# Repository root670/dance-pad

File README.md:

# 8020 Extruded Aluminum Dance Pad

*StepMania: Way more fun than a Pelaton bike.*

4-panel dance pad project using a frame built out of 30mm profile 8020
("T-Slot") extruded aluminum including a bar with 9 arrow panels following a
similar design to StepManiaX pads. Each directional arrow has a PCB containing
25 WS2812B RGB LEDs and 4 FSR sensors connected to a Main PCB that acts as a
breakout for a Teensy 4.1.

The firmware reads values from 16 sensors and reports them as gamepad inputs.
I'm using homemade sensors created with two 150mm strips of 1/4" copper tape
attached to 160mm x 20mm transparency film with 4mil Velostat placed across the
top. Wires are soldered to each of the copper tape strips and terminate to
JST-XE connectors at the end to connect to the Arrow Panel PCB. According to
papers I've read, creating FSR in this way will likely lead to less drifting
over time compared to "sandwich" style sensors where Velostat is placed between
two pieces of copper tape. This is similar to the method used by
commercially-produced FSRs.

## Motivation

There has been a ton of interest in using force sensitive resistors in dance
pads recently to replace contact-based sensors and many designs have been
created. I decided to create a design for a full pad that is durable but doesn't
require power tools to build. I also wanted to gain experience using Inventor
and KiCad and share my design with others who may find it useful. It's certainly
not the best design, but the experience I've gained in the process is
invaluable.

Having personal projects to come back to is a great and productive way to
improve your creative and technical skills, especially during COVID times. And
when the project involves maintaining your physical health, that's even better! I
can't stress enough how rewarding it is to start a project, work on in over the
course of a few months, and see it through to completion. Soapbox aside, I
highly recommend attempting projects for things that seem slightly out of your
abilities. You might be surprised what you're capable of if you stick with it.

## Directory Structure

* `Frame`: Inventor project for the aluminum frame. It houses nine 276mm x 276mm
  x 12mm cast acrylic panels with 2mm clearance between each edge. The back of
  the frame has slots for securing a bar.

* `Arrow PCB`: 2 layer 200mm x 200mm PCB used within each arrow containing 25
  WS2812B V5 LEDs arranged in an alternating 4,3 grid pattern and pins for 4
  FSRs connected using JST-XH and JST-ZE connectors. Created in KiCad. Each FSR
  uses a 330 ohm pull down resistor to ground. The board is connected to the
  Main PCB using a CAT6 cable for the four sensors and screw terminals for the
  LED power, ground, and data lines. The PCB can be rotated to the best location
  to route wires to the Main PCB by denoting the location in the firmware.
  M4-sized terminals are on the corners of the PCB so it can be mounted to the
  frame using 3D printed parts (TODO).

* `Main PCB`: 2 layer ~100mm x ~100mm breakout board for a Teensy 4.1. Wires
  RJ45 connectors for connections coming from 4 Arrow PCBs and screw terminals
  for up 5 LED strands interfaced through 3.3V to 5V logic converters. The
  sensor wires are decoupled with 3.3v wires in the cable to minimize
  interference. Has M4-sized screw terminal to attach to 3D printed mounting
  hardware (TODO).

* `Configurator`: Application to configure and debug the pad written in Python.
  Communicates with the firmware using a serial connection.

* `Firmware`: Code that runs on the Teensy. Reads sensor values, listens for
  serial messages, and controls the LEDs. Uses fixed timings for sending Joypad
  reports and updating the LEDs. The goal is for it to be easy enough to modify
  to support different pad layouts (i.e. 5 panel StepManiaX or Pump It Up pads)

* `Supplemental`: Various helper scripts and files related to this project. All
  of these are optional but may be useful depending on you setup.

## Status

The frame, acrylic panels, and PCB designs have been finalized, fabricated, and
assembled.

The arrows have counter bore screws but I made the larger part of the counter
bore too small (It's a 9.53mm counterbore for a 7.94mm through hole, leaving
~0.8mm radius for the counterbore. Whoops.). It's large enough to fit
button-head M5 screws with a 3D printed spacer but M6 socket and button head
screws will not fit unfortunately. These will work fine with M5 screws but the
lesson learned is to not hastily order things like this in the future :-).

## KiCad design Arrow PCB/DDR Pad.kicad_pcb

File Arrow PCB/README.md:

# Arrow Panel PCB

Board placed under each panel. Houses 25 WS2812B V5 RGB LEDs and connects to 4
FSR sensors using JST-XE or JST-ZH connectors. Connects back to the Main PCB
using a CAT6 cable for the sensors and cables secured to a screw terminal for
the lights.

## Notes

* The pull down resistor used for each sensor may need to be adjusted depending
  on the sensors being used.
* The board requires the "V5" revision of the WS2812B LEDs. The advantage of
  this version is that have an internal capacitor so you don't the need to place
  an external capacitor between the positive voltage and ground pins. If an
  older version is used the LEDs will likely be damaged when they receive power.

## Issues

* I was unable to get the LEDs to work reliably using multiple 3.3v and 5v
  microcontrollers and WS2812B libraries. I believe there is something wrong
  with my design or the LEDs sourced by LCSC were not actually the 5V
  variations. LCSC has been unable to confirm if they are actually the V5
  version.
* The PCB is too big to fit within the frame underneath the panels when using
  corner brackets. As a workaround the PCBs need to be placed underneath the
  frame.

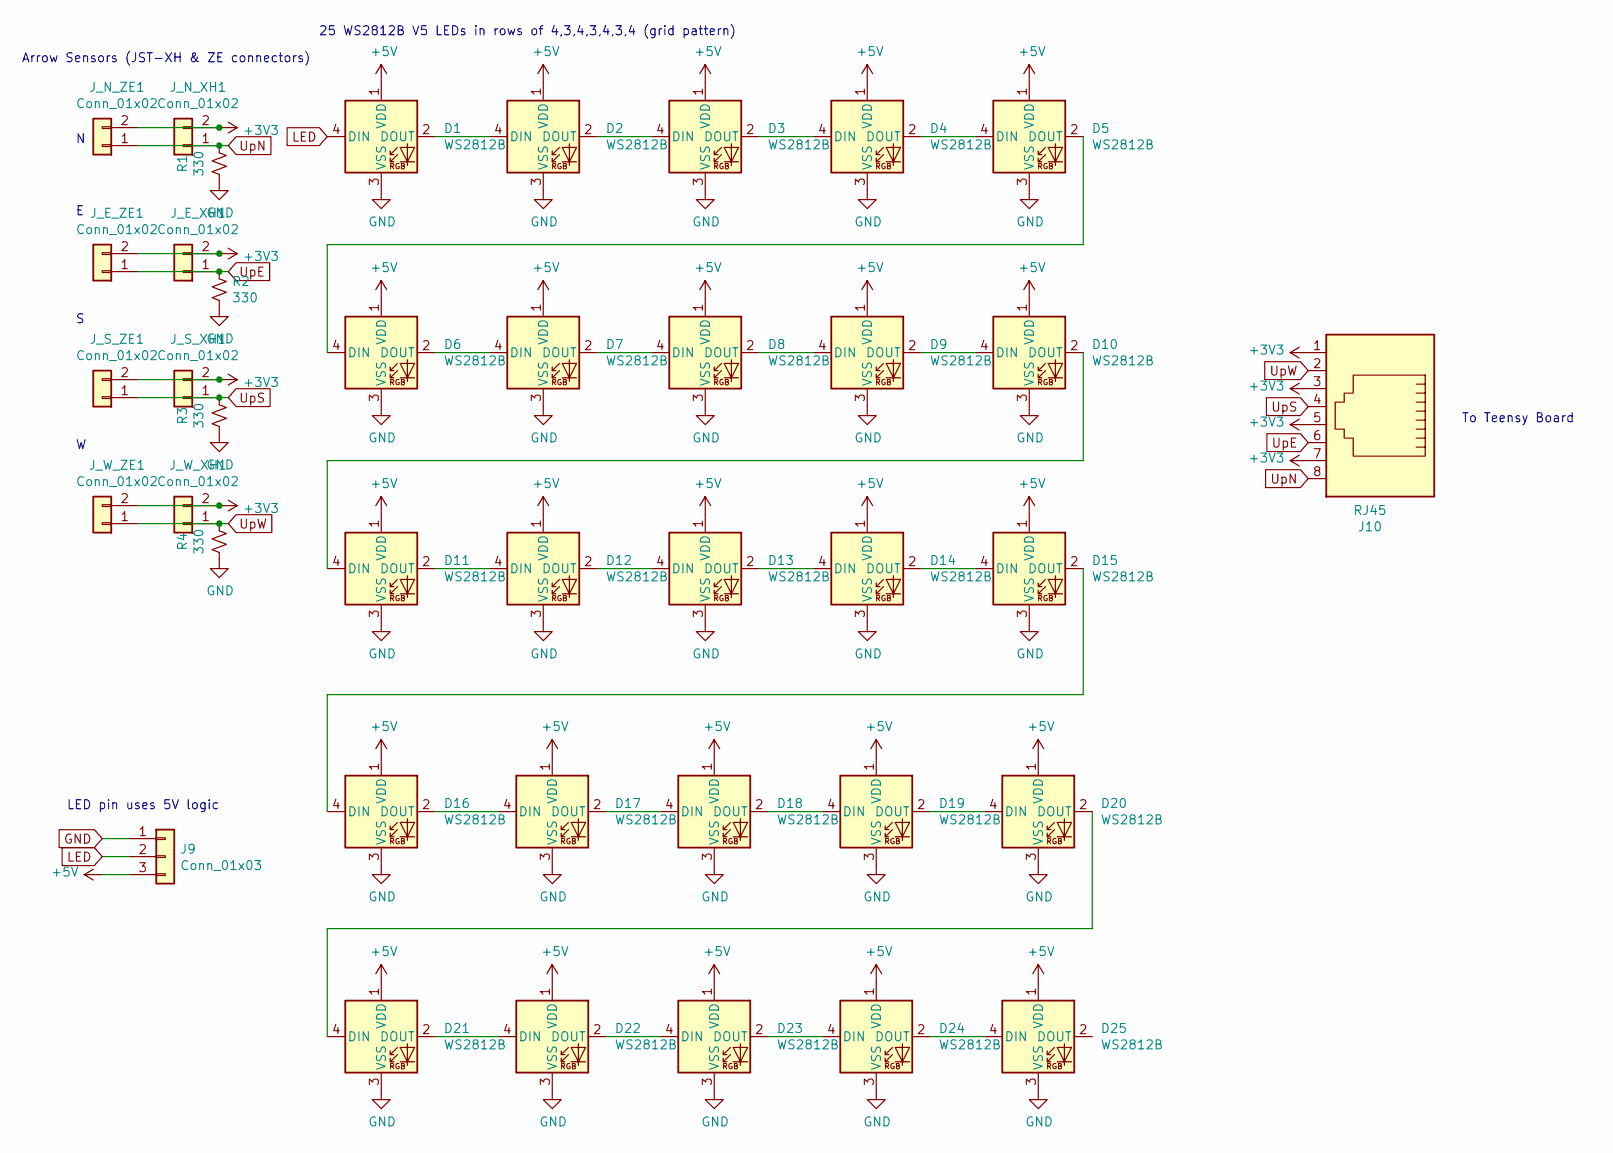
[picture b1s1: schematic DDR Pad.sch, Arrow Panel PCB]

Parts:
D1, D2, D3, D4, D5, D6, D7, D8, D9, D10, D11, D12, D13, D14, D15, D16, D17, D18, D19, D20, D21, D22, D23, D24, D25: WS2812B; LED_WS2812B_PLCC4_5.0x5.0mm_P3.2mm
J9: Conn_01x03; 1935174
J10: RJ45; AMPHENOL_RJHSE-5080
J_E_XH1: Conn_01x02; JST_XH_B2B-XH-A_1x02_P2.50mm_Vertical
J_E_ZE1: Conn_01x02; JST_ZE_B02B-ZESK-1D_1x02_P1.50mm_Vertical
J_N_XH1: Conn_01x02; JST_XH_B2B-XH-A_1x02_P2.50mm_Vertical
J_N_ZE1: Conn_01x02; JST_ZE_B02B-ZESK-1D_1x02_P1.50mm_Vertical
J_S_XH1: Conn_01x02; JST_XH_B2B-XH-A_1x02_P2.50mm_Vertical
J_S_ZE1: Conn_01x02; JST_ZE_B02B-ZESK-1D_1x02_P1.50mm_Vertical
J_W_XH1: Conn_01x02; JST_XH_B2B-XH-A_1x02_P2.50mm_Vertical
J_W_ZE1: Conn_01x02; JST_ZE_B02B-ZESK-1D_1x02_P1.50mm_Vertical
R1, R2, R3, R4: 330; R_0603_1608Metric

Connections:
+3V3: J10.1, J10.3, J10.5, J10.7, J_E_XH1.2, J_E_ZE1.2, J_N_XH1.2, J_N_ZE1.2, J_S_XH1.2, J_S_ZE1.2, J_W_XH1.2, J_W_ZE1.2
+5V: D1.1 (VDD), D2.1 (VDD), D3.1 (VDD), D4.1 (VDD), D5.1 (VDD), D6.1 (VDD), D7.1 (VDD), D8.1 (VDD), D9.1 (VDD), D10.1 (VDD), D11.1 (VDD), D12.1 (VDD), D13.1 (VDD), D14.1 (VDD), D15.1 (VDD), D16.1 (VDD), D17.1 (VDD), D18.1 (VDD), D19.1 (VDD), D20.1 (VDD), D21.1 (VDD), D22.1 (VDD), D23.1 (VDD), D24.1 (VDD), D25.1 (VDD), J9.3
GND: D1.3 (VSS), D2.3 (VSS), D3.3 (VSS), D4.3 (VSS), D5.3 (VSS), D6.3 (VSS), D7.3 (VSS), D8.3 (VSS), D9.3 (VSS), D10.3 (VSS), D11.3 (VSS), D12.3 (VSS), D13.3 (VSS), D14.3 (VSS), D15.3 (VSS), D16.3 (VSS), D17.3 (VSS), D18.3 (VSS), D19.3 (VSS), D20.3 (VSS), D21.3 (VSS), D22.3 (VSS), D23.3 (VSS), D24.3 (VSS), D25.3 (VSS), J9.1, R1.2, R2.2, R3.2, R4.2
LED: D1.4 (DIN), J9.2
unnamed: D1.2 (DOUT), D2.4 (DIN)
unnamed: D2.2 (DOUT), D3.4 (DIN)
unnamed: D3.2 (DOUT), D4.4 (DIN)
unnamed: D4.2 (DOUT), D5.4 (DIN)
unnamed: D5.2 (DOUT), D6.4 (DIN)
unnamed: D6.2 (DOUT), D7.4 (DIN)
unnamed: D7.2 (DOUT), D8.4 (DIN)
unnamed: D8.2 (DOUT), D9.4 (DIN)
unnamed: D10.2 (DOUT), D11.4 (DIN)
unnamed: D9.2 (DOUT), D10.4 (DIN)
unnamed: D11.2 (DOUT), D12.4 (DIN)
unnamed: D12.2 (DOUT), D13.4 (DIN)
unnamed: D13.2 (DOUT), D14.4 (DIN)
unnamed: D14.2 (DOUT), D15.4 (DIN)
unnamed: D15.2 (DOUT), D16.4 (DIN)
unnamed: D16.2 (DOUT), D17.4 (DIN)
unnamed: D17.2 (DOUT), D18.4 (DIN)
unnamed: D18.2 (DOUT), D19.4 (DIN)
unnamed: D19.2 (DOUT), D20.4 (DIN)
unnamed: D20.2 (DOUT), D21.4 (DIN)
unnamed: D21.2 (DOUT), D22.4 (DIN)
unnamed: D22.2 (DOUT), D23.4 (DIN)
unnamed: D23.2 (DOUT), D24.4 (DIN)
unnamed: D24.2 (DOUT), D25.4 (DIN)
UpE: J10.6, J_E_XH1.1, J_E_ZE1.1, R2.1
UpN: J10.8, J_N_XH1.1, J_N_ZE1.1, R1.1
UpS: J10.4, J_S_XH1.1, J_S_ZE1.1, R3.1
UpW: J10.2, J_W_XH1.1, J_W_ZE1.1, R4.1

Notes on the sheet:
LED pin uses 5V logic
Arrow Sensors (JST-XH & ZE connectors)
25 WS2812B V5 LEDs in rows of 4,3,4,3,4,3,4 (grid pattern)
To Teensy Board

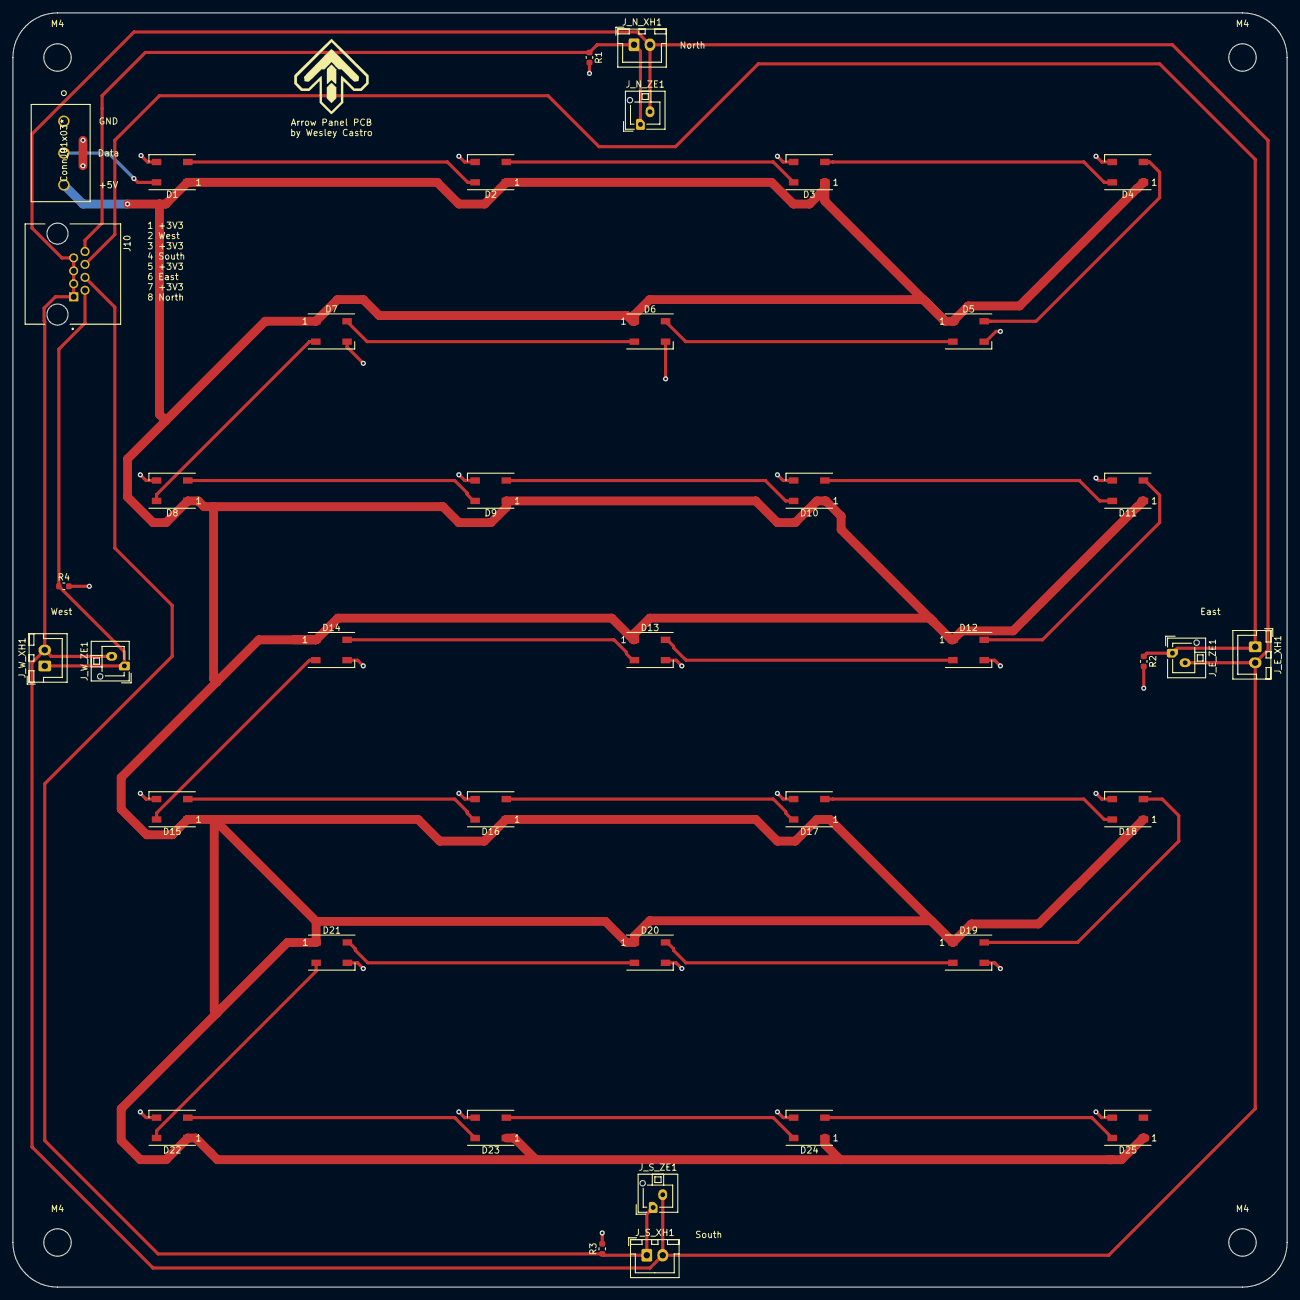
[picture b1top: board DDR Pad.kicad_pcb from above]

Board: 2 copper layers, 200.0 x 200.0 mm, 43 parts (0 on the bottom side), 32 nets.

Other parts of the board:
M4, M4#2, M4#3, M4#4: MountingHole_4.3mm_M4

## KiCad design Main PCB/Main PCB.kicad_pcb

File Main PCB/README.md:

# Main PCB

Breakout board for a Teensy 4.1 with 4 RJ45 connectors to connect the sensors
from each arrow and 5 3-pin screw terminals to connect the lights. An additional
3-pin screw terminal is available for an auxilary lighting strip.

## Notes

* At least a 6A 5V DC power supply is needed to support displaying all LEDs at
  maximum brightness.

## Issues

* The LED pins for the four arrows  don't allow for "parallel output" with
  FastLED or WS2812Serial because I didn't realize only a subset of pins support
  that feature. The AuxLED pin however should work with parallel output.
* Silkscreen labels are missing for most connectors.

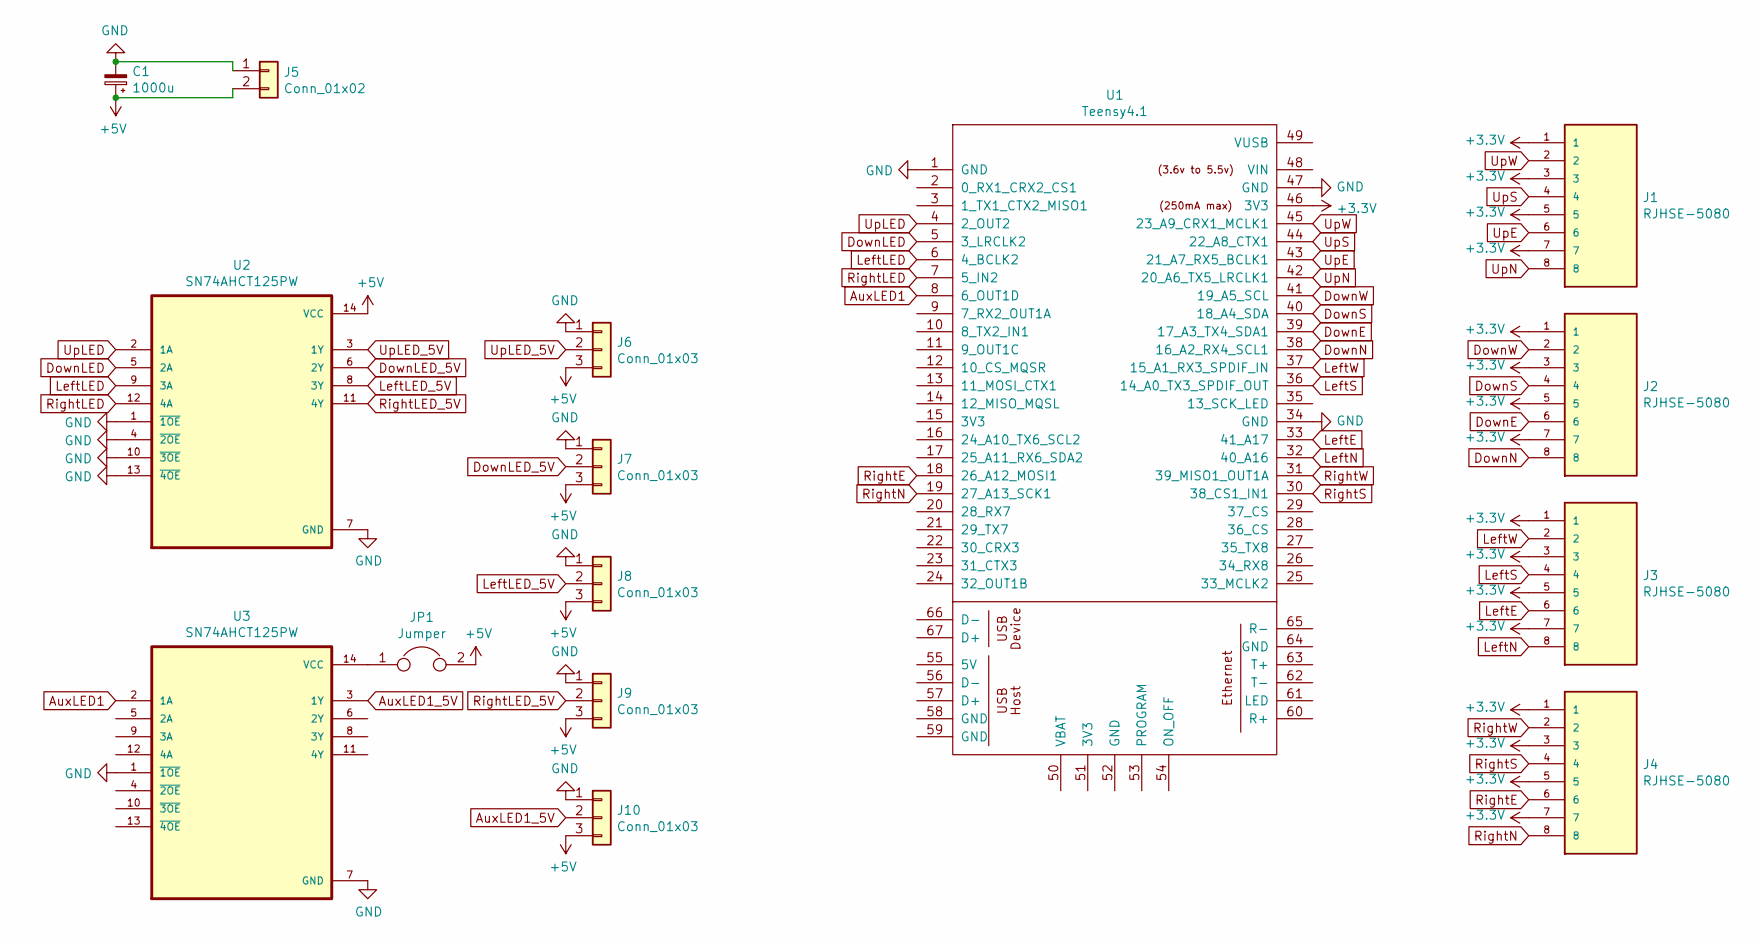
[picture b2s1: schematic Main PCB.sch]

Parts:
C1: 1000u; CP_Elec_8x10; LCSC C134755
J1, J2, J3, J4: RJHSE-5080; AMPHENOL_RJHSE-5080; PARTREV G
J5: Conn_01x02; 1935161
J6, J7, J8, J9, J10: Conn_01x03; 1935174
JP1: Jumper; PinHeader_1x02_P2.54mm_Vertical
U1: Teensy4.1; Teensy41
U2, U3: SN74AHCT125PW; SOP65P640X120-14N

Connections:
+3V3: J1.1, J1.3, J1.5, J1.7, J2.1, J2.3, J2.5, J2.7, J3.1, J3.3, J3.5, J3.7, J4.1, J4.3, J4.5, J4.7, U1.46 (3V3)
+5V: C1.1, J5.2, J6.3, J7.3, J8.3, J9.3, J10.3, JP1.2, U2.14 (VCC)
AuxLED1: U1.8 (6_OUT1D), U3.2 (1A)
AuxLED1_5V: J10.2, U3.3 (1Y)
DownE: J2.6, U1.39 (17_A3_TX4_SDA1)
DownLED: U1.5 (3_LRCLK2), U2.5 (2A)
DownLED_5V: J7.2, U2.6 (2Y)
DownN: J2.8, U1.38 (16_A2_RX4_SCL1)
DownS: J2.4, U1.40 (18_A4_SDA)
DownW: J2.2, U1.41 (19_A5_SCL)
GND: C1.2, J5.1, J6.1, J7.1, J8.1, J9.1, J10.1, U1.1 (GND), U1.34 (GND), U1.47 (GND), U2.1 (~1OE), U2.4 (~2OE), U2.7 (GND), U2.10 (~3OE), U2.13 (~4OE), U3.1 (~1OE), U3.7 (GND)
LeftE: J3.6, U1.33 (41_A17)
LeftLED: U1.6 (4_BCLK2), U2.9 (3A)
LeftLED_5V: J8.2, U2.8 (3Y)
LeftN: J3.8, U1.32 (40_A16)
LeftS: J3.4, U1.36 (14_A0_TX3_SPDIF_OUT)
LeftW: J3.2, U1.37 (15_A1_RX3_SPDIF_IN)
unnamed: JP1.1, U3.14 (VCC)
RightE: J4.6, U1.18 (26_A12_MOSI1)
RightLED: U1.7 (5_IN2), U2.12 (4A)
RightLED_5V: J9.2, U2.11 (4Y)
RightN: J4.8, U1.19 (27_A13_SCK1)
RightS: J4.4, U1.30 (38_CS1_IN1)
RightW: J4.2, U1.31 (39_MISO1_OUT1A)
UpE: J1.6, U1.43 (21_A7_RX5_BCLK1)
UpLED: U1.4 (2_OUT2), U2.2 (1A)
UpLED_5V: J6.2, U2.3 (1Y)
UpN: J1.8, U1.42 (20_A6_TX5_LRCLK1)
UpS: J1.4, U1.44 (22_A8_CTX1)
UpW: J1.2, U1.45 (23_A9_CRX1_MCLK1)

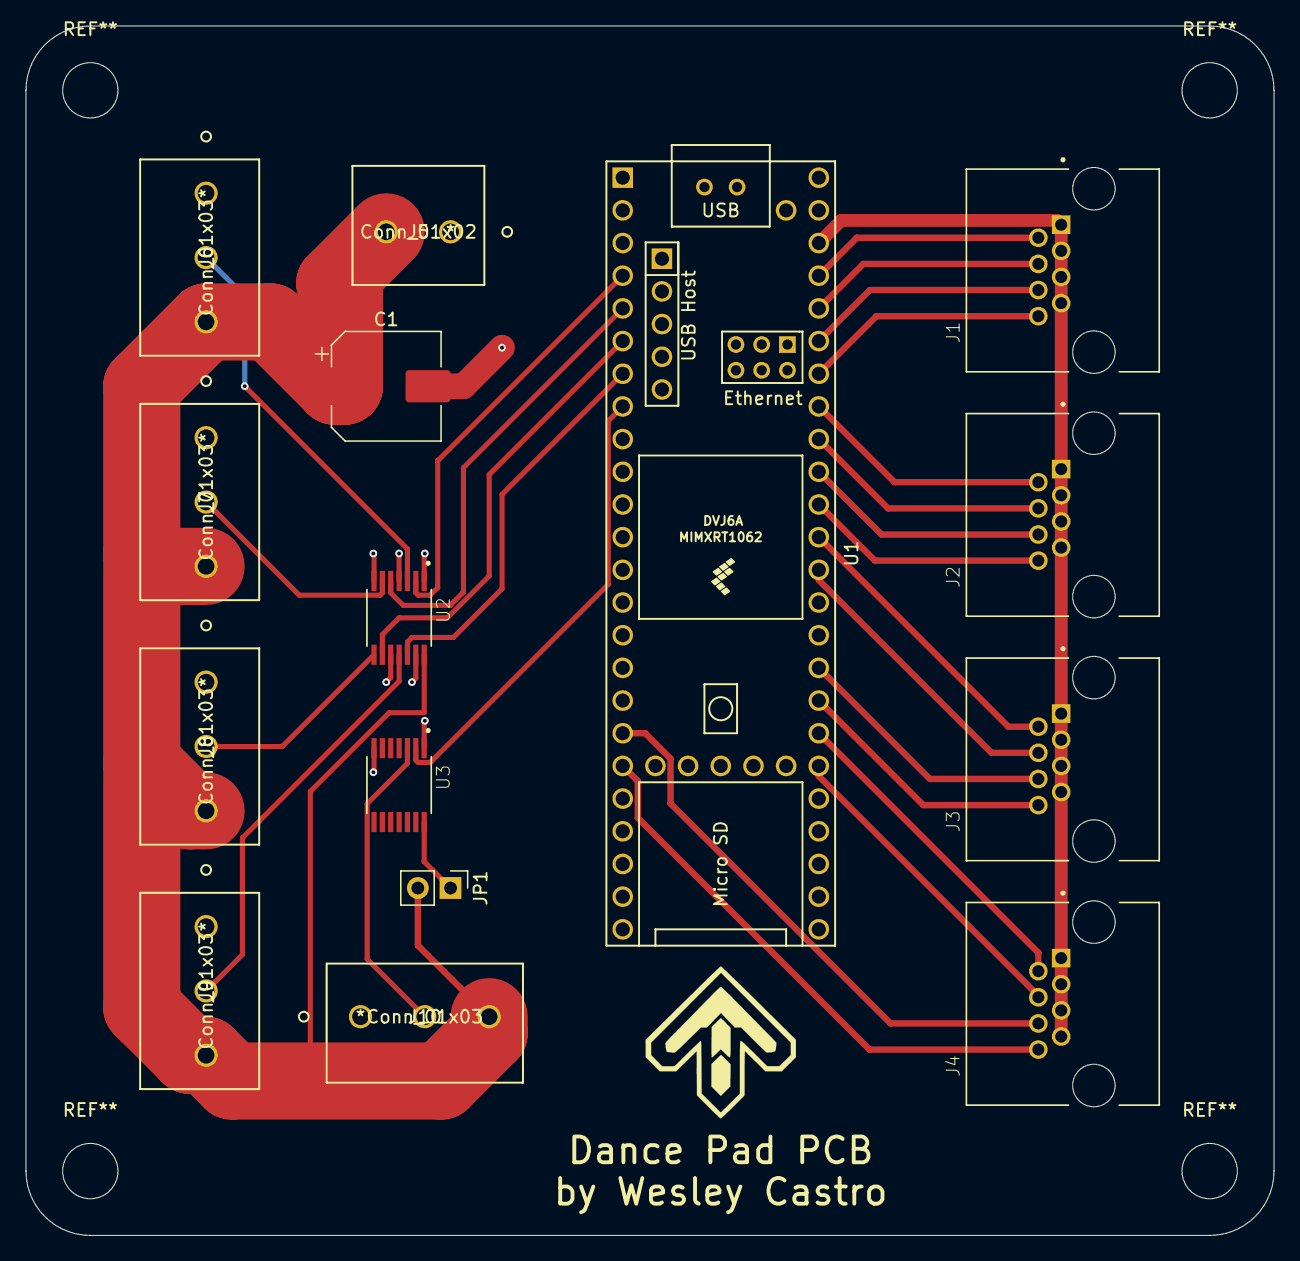
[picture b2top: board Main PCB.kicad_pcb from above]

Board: 4 copper layers, 97.0 x 94.0 mm, 15 parts (0 on the bottom side), 30 nets.

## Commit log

2020-11-25 Update README.md. Add MIT license.
2020-11-25 Add frame.
2020-11-25 Add image of frame to README.md.
2020-11-25 Remove old bill of materials.
2020-11-25 Fix typo.
2020-11-25 Update Arrow schematic. Add schematic images.
2020-11-25 Add README.md to PCB projects.
2020-11-26 Add tests.
    Remove default argument for Serial object.
2020-11-27 Add config loader.
2020-11-27 Add skeleton for frontend.
2020-12-06 Reorganize configuratior.
    Planning to use PyQT for the tool instead of a web-based UI.
2020-12-06 Change PCB orientation. Ignore lights for now.
2020-12-06 Fix tests.
2020-12-06 Use const value for command string.
2020-12-06 Add tests for PanelOrientation.
2020-12-06 Add requirements.txt
2020-12-06 Update prose.
2020-12-06 Add placeholder for GUI.
2020-12-08 Working on the PyQT configurator.
2020-12-24 Center analog controls and d-pad.
2020-12-24 Implement configuration class.
2020-12-24 Use per-sensor thresholds.
2020-12-24 Remove unused variables.
2020-12-24 Make variable static.
2020-12-24 Cleanup and fix warnings.
2020-12-24 Add SerialProcessor class.
2020-12-24 Remove unneded calibration.
    The sensors will automatically calibrate the first time update() is called.
2020-12-24 Load UI from .ui file. Add combobox for devices.
2020-12-24 Status updates.
2020-12-24 Define string constants.
2020-12-25 Add `set` command. Create functions for each command.
2020-12-25 Get/set 16-bit unsigned values.
2020-12-25 Add Configuration::toString().
2020-12-25 Get trigger/release thresholds from global config.
2020-12-25 Save default to config if unset.
2020-12-25 Add `persist` command.
2020-12-25 Don't send blank responses.
2020-12-25 Fix dirty flag usage.
2020-12-25 Get trigger/release setting at each calibration.
2020-12-25 Refactor retrieving sensor status.
2020-12-25 Read config during `setup()`.
2020-12-25 Reduce memory usage by half!
2020-12-25 Add missing include.
2020-12-25 Move most to private lib.
2020-12-25 Report pins used for sensors.
    Can be used to set config values referencing pin numbers (i.e. the trigger/release thresholds for each sensor).
2020-12-25 Return status from set command.
2020-12-25 Read new value command response.
    Add `set_thresholds` function.
2020-12-26 Fix tests
2020-12-27 Add tests for `Communicator.set_thresholds`.
2020-12-27 Plot data for 16 sensors
2020-12-27 Add value table.
2020-12-27 Use more realistic test data.
2020-12-27 Update table
2020-12-28 Convert config to singleton. Bug fixes.
2020-12-28 Read values from serial device.
2021-01-09 Report thresholds
2021-01-09 Increase default threshold.
2021-01-09 Calibrate panels in setup().
2021-01-13 Decrease thresholds.
2021-01-13 Reset sensor after calibrating.
2021-01-13 Cleanup calibrate command.
2021-01-13 Add button to calibrate pad.
2021-01-13 Fix plot and table.
2021-01-13 Fix running on Windows 10 2004.
2021-01-13 Don't print FPS.
2021-01-13 Add lighting code.
    Decode light data and use FastLED with a OctoWS2812B-derived controller to drive LEDs in each panel.
2021-01-16 Fix Configuration::getUInt32().
2021-01-16 Add callback system to Configuration.
2021-01-16 Decrease sensitivity a bit
2021-01-16 Convert Lights to singleton class.
2021-01-19 Fix removing trailing space.
2021-01-19 Set uint32 configuration values.
2021-01-19 Get color configuration.
2021-01-19 Create Serial object from string.
2021-01-19 Add `set_color()` and `set_arrow_lights()` methods
2021-01-19 Add lighting controls.
2021-01-20 Fade existing lights before illuminating.
2021-01-20 Fix left panel orientation.
2021-01-22 Color-correct lights for more accurate colors.
    Colors chosen in the configurator are much closer to the lights show in the pad now!
2021-01-26 Add Config::reset(). Fix u16 values not being saved.
2021-01-26 Add `-reset` command.
2021-01-26 Add comment about ADC read times.
2021-02-10 Add supplemental files.
2021-02-10 Increase lighting brightness.
2021-02-10 Decrease sensitivity a little bit.
2021-02-10 Notify callbacks when config is reset.
2021-02-10 Update README.md.
2021-02-10 Remove planned features list.
2021-02-10 Indent with spaces.
2022-11-20 Configure brightness
2022-11-20 Add option to toggle lights in the pad.
2022-11-21 Don't write when resetting.
2023-04-06 Set individual trigger/release thresholds. Add persist button.
2023-04-12 Ignore .DS_Store
2023-04-12 Upgrade to QT6. Update dependencies.
2023-11-22 Remove prints from lights_bridge.py
    Was leading to latency regression.
2024-08-22 Formatting. Use keyboard instead of joystick
2024-08-31 Formatting. Bugfixes.

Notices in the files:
parts and their libraries:
Copyright 2016 Accelerated Designs. All rights reserved.
